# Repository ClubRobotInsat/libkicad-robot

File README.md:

# Kicad library of the Robot club at INSA Toulouse

## How to create a new component

1. Install the library on your computer
2. Use the footprint / symbol editor to create the components
3. Copy the components from the 3rd party folder (Preference -> Configure Paths -> KICAD7_3RD_PARTY) to this repository
4. Update the file VERSION to bump version and allows everyone to update the plugin

## How to bring 3D model

For 3D model it's a bit more complicated, you must add the model manualy in the correct folder in this repository and in the footprint editor 
refer to it with something like `${KICAD7_3RD_PARTY}/3dmodels/com_github_clubrobotinsat_libkicad-robot/Robot.3dshapes/YOURMODEL.step`

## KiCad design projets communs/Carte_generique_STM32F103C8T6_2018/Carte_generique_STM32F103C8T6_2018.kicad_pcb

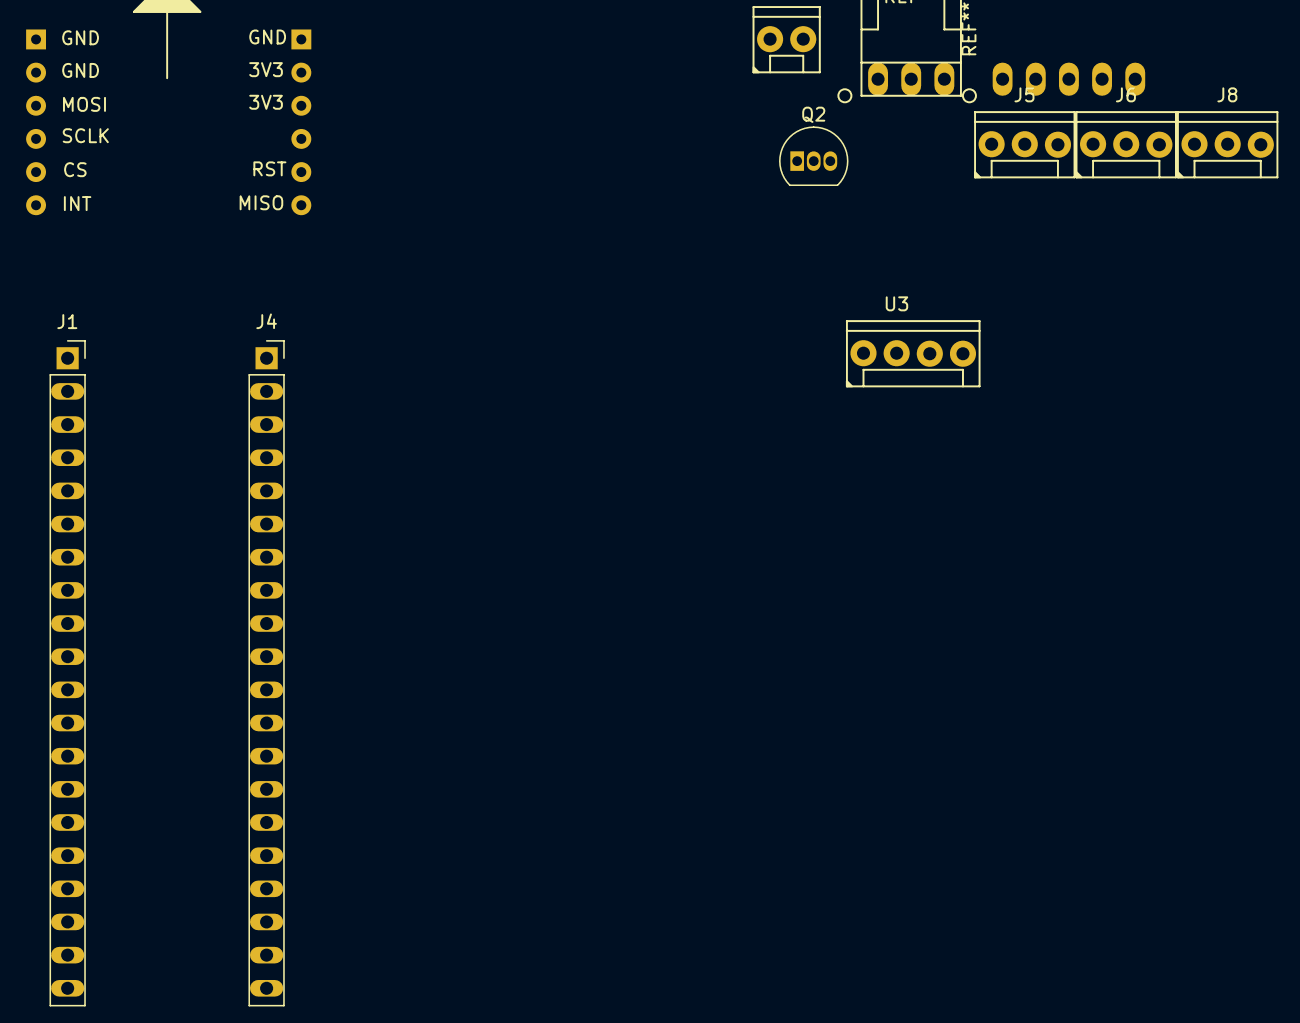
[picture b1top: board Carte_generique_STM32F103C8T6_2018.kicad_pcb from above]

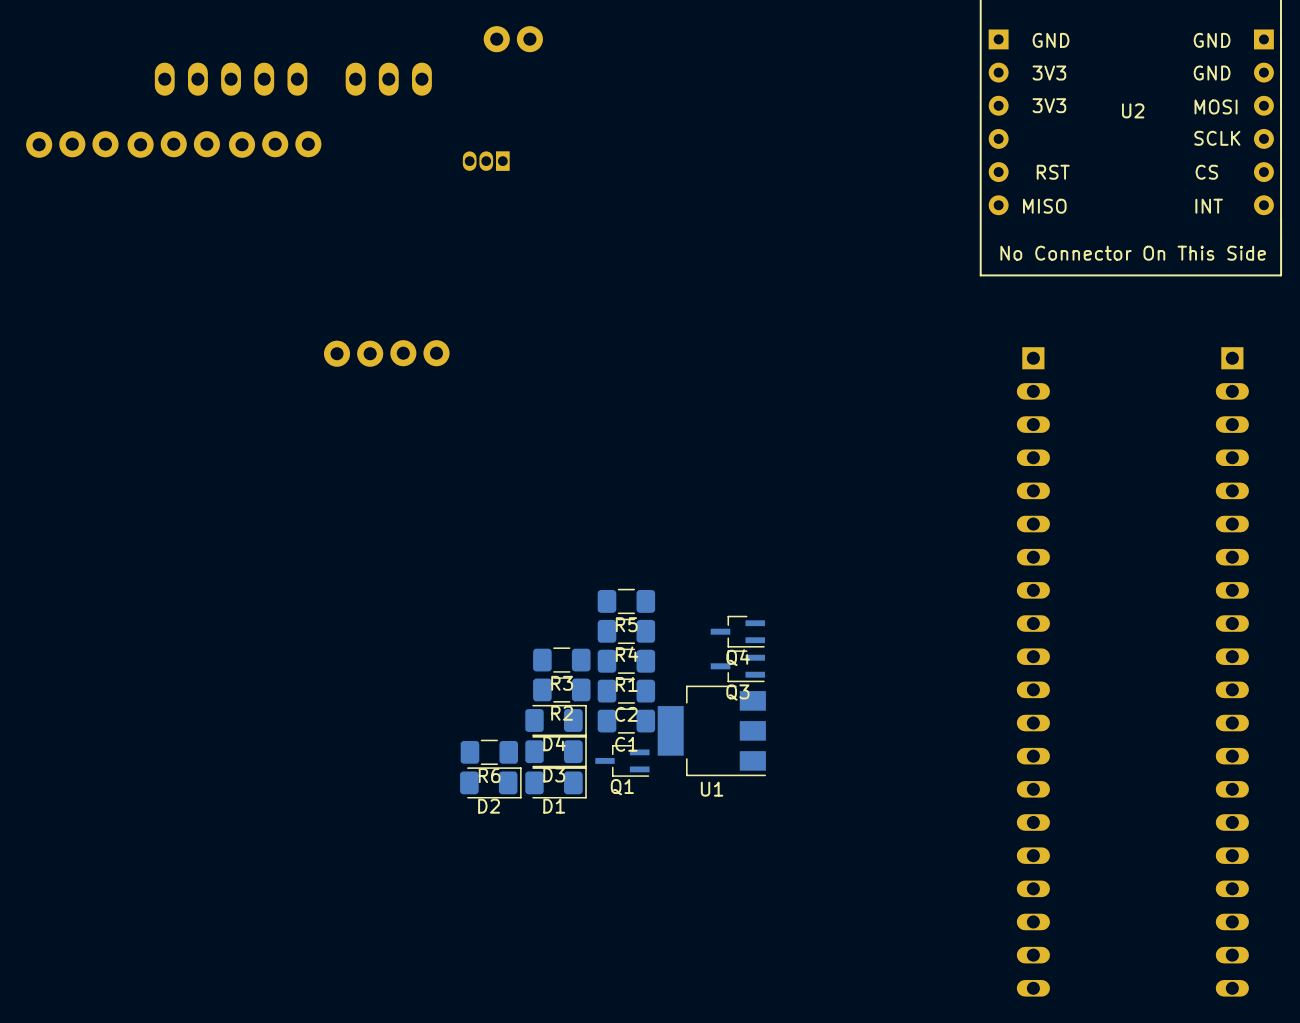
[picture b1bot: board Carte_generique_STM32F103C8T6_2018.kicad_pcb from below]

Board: 2 copper layers, 27 parts (16 on the bottom side), 12 nets, no tracks yet.

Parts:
C1, C2: 1u; C_1206_3216Metric_Pad1.42x1.75mm_HandSolder
D1: LED_hardfault_jaune; LED_1206_3216Metric_Pad1.42x1.75mm_HandSolder
D2: LED_communication_vert; LED_1206_3216Metric_Pad1.42x1.75mm_HandSolder
D3: led_feedback_vert; LED_1206_3216Metric_Pad1.42x1.75mm_HandSolder
D4: LED_alimentation_rouge; LED_1206_3216Metric_Pad1.42x1.75mm_HandSolder
J1, J4: Conn_01x20_Female; PinSocket_1x20_P2.54mm_Vertical_Long_Pads
J2: Alim puissance; HE14-2-straight
J3: Alim logique; HE14-3_horizontal
J5: PWM input; HE14-3-straight
J6: PWM output; HE14-3-straight
J7: QEI; HE14-5_horizontal
J8: Liaison serie; HE14-3-straight
Q1, Q3, Q4: PMF370XN; SOT-323_SC-70_Handsoldering
Q2: 2N7000; TO-92_Inline
R1, R4, R5, R6: 150; R_1206_3216Metric_Pad1.42x1.75mm_HandSolder
R2, R3: 10k; R_1206_3216Metric_Pad1.42x1.75mm_HandSolder
U1: TC1262-33; SOT-223-3_TabPin2
U2: w5500
U3: servo_connector; HE14-4-straight

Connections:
+3V3: C2.1, Q2.2, R2.1, U1.3, U2.10, U2.11
+5V: C1.1, J1.18, J3.2, J7.2, R1.1, R3.1, R4.1, R5.1, R6.1, U1.1
/3.3V_logic: Q2.1, R2.2
/5V_logic: Q2.3, R3.2
GND: C1.2, C2.2, D4.1, J1.19, J3.1, J4.1, J4.2, J5.1, J6.1, J7.1, J8.1, Q1.2, Q3.2, Q4.2, U1.2, U2.5, U2.6, U2.12, U3.1
unnamed: D1.1, Q1.3
unnamed: D1.2, R1.2
unnamed: D2.1, Q3.3
unnamed: D2.2, R4.2
unnamed: D3.1, Q4.3
unnamed: D3.2, R5.2
unnamed: D4.2, R6.2

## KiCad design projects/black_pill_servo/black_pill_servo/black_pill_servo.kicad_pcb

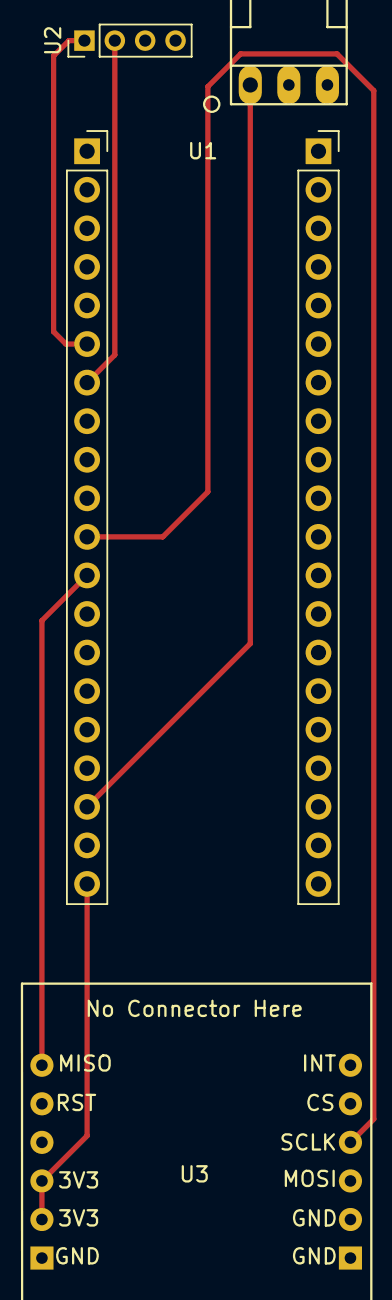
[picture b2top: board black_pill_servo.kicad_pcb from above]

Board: 2 copper layers, 4 parts (0 on the bottom side), 8 nets.

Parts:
J1: alim_logique_5V; HE14-3_horizontal
U1: black_pill
U2: servo_connector; PinHeader_1x04_P2.00mm_Vertical
U3: w5500

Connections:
+3V3: U1.20, U3.10, U3.11
+5V: J1.1, U1.18
GND: J1.2, U1.19, U1.21, U1.22, U2.4, U3.5, U3.6, U3.12
MISO: U1.12, U3.7
MOSI: U1.13, U3.4
PA9: U1.6, U2.1
PA10: U1.7, U2.2
SCLK: U1.11, U3.3

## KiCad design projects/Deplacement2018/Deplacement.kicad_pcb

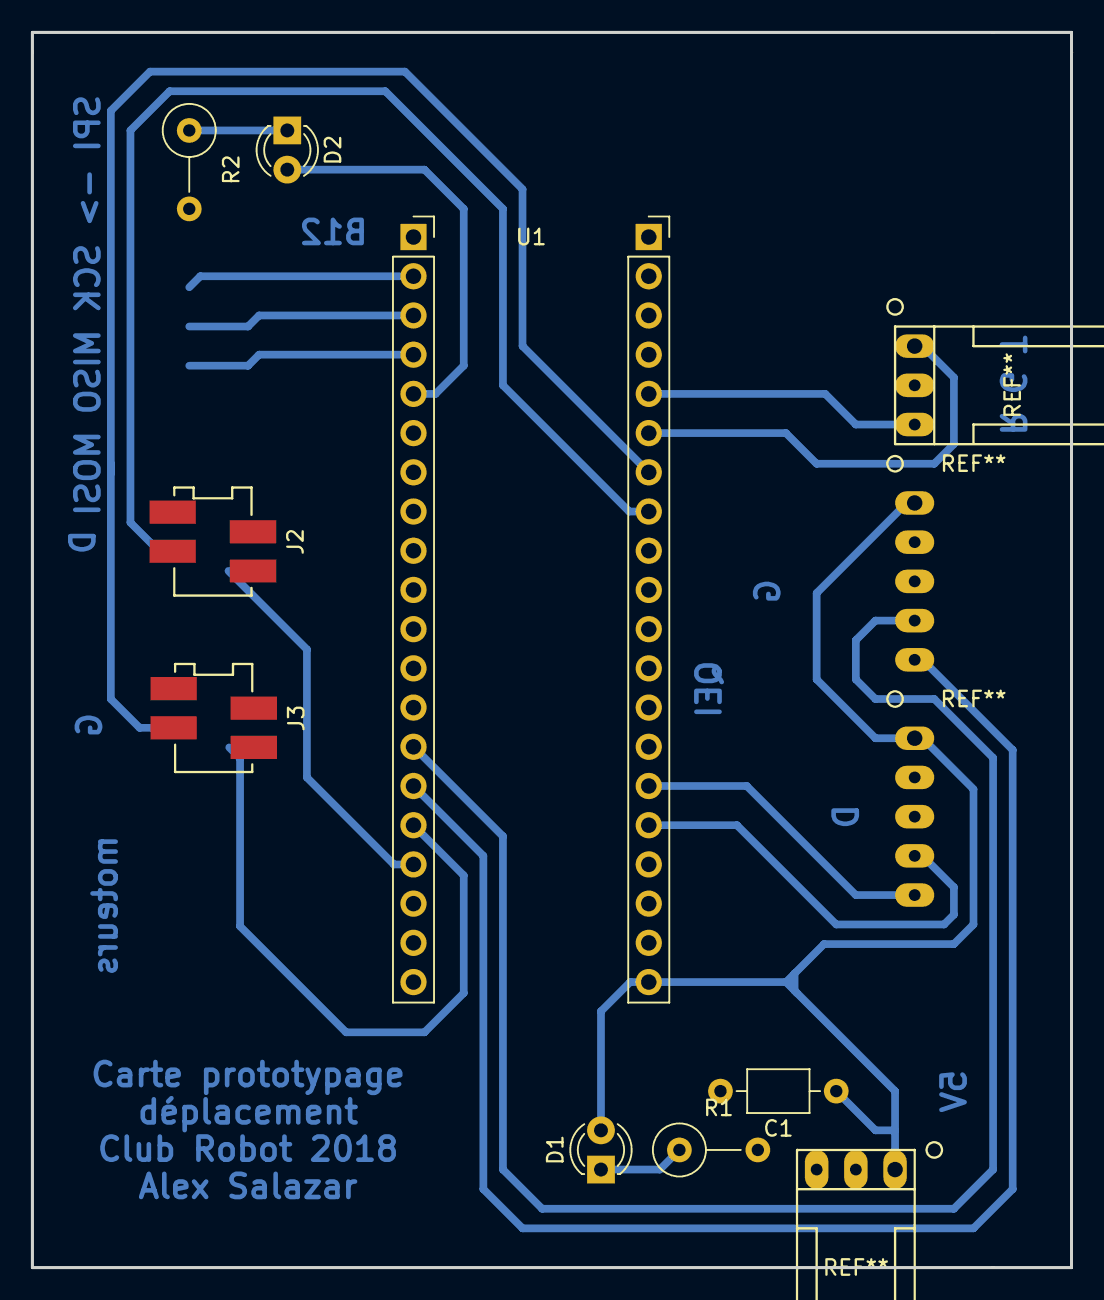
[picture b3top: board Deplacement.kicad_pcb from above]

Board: 2 copper layers, 67.3 x 80.0 mm, 12 parts (0 on the bottom side), 15 nets.

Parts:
C1: C; C_Axial_L3.8mm_D2.6mm_P7.50mm_Horizontal
D1, D2: LED; LED_D3.0mm
J1: alim_logique_5V; HE14-3_horizontal
J2: moteur_droit; ConnectorMicromatch-4
J3: moteur_gauche; ConnectorMicromatch-4
J4: Conn_01x03; HE14-3_horizontal
J5: QEI_droite; HE14-5_horizontal
J6: QEI_gauche; HE14-5_horizontal
R1, R2: R; R_Axial_DIN0309_L9.0mm_D3.2mm_P5.08mm_Vertical
U1: black_pill

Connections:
+5V: C1.1, D1.2, J1.1, J5.1, J6.1, U1.40
Direction_moteur_droit: J2.1, U1.17
Direction_moteur_gauche: J3.1, U1.16
GND: C1.2, J1.2, J2.3, J3.3, J4.2, J5.2, J6.2, R1.2, R2.2, U1.19, U1.21, U1.22
LED_feedback: D2.2, U1.5
unnamed: D1.1, R1.1
unnamed: D2.1, R2.1
PWM_moteur_droit: J2.2, U1.28
PWM_moteur_gauche: J3.2, U1.27
QEI_droite_1: J5.4, U1.36
QEI_droite_2: J5.5, U1.35
QEI_gauche_1: J6.4, U1.14
QEI_gauche_2: J6.5, U1.15
RX: J4.3, U1.25
TX: J4.1, U1.26

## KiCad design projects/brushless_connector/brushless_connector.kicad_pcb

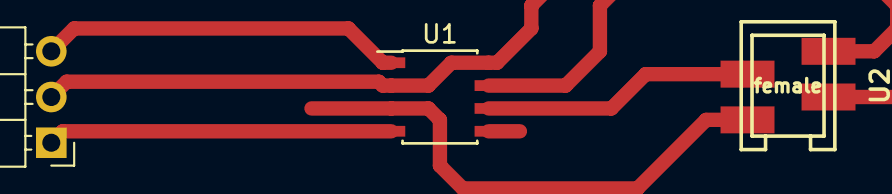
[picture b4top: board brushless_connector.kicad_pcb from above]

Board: 2 copper layers, 3 parts (0 on the bottom side), 6 nets.

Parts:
J1: Conn_01x03_Female; PinHeader_1x03_P2.54mm_Horizontal
U1: MCP2551-I-SN; SOIC-8_3.9x4.9mm_P1.27mm
U2: micromatch_female; 0-188275-4_SMD_4-pin_female

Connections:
GND: J1.2, U1.2, U1.8, U2.2
unnamed: J1.1, U1.4
unnamed: J1.3, U1.1
unnamed: U1.3, U2.1
unnamed: U1.6, U2.3
unnamed: U1.7, U2.4

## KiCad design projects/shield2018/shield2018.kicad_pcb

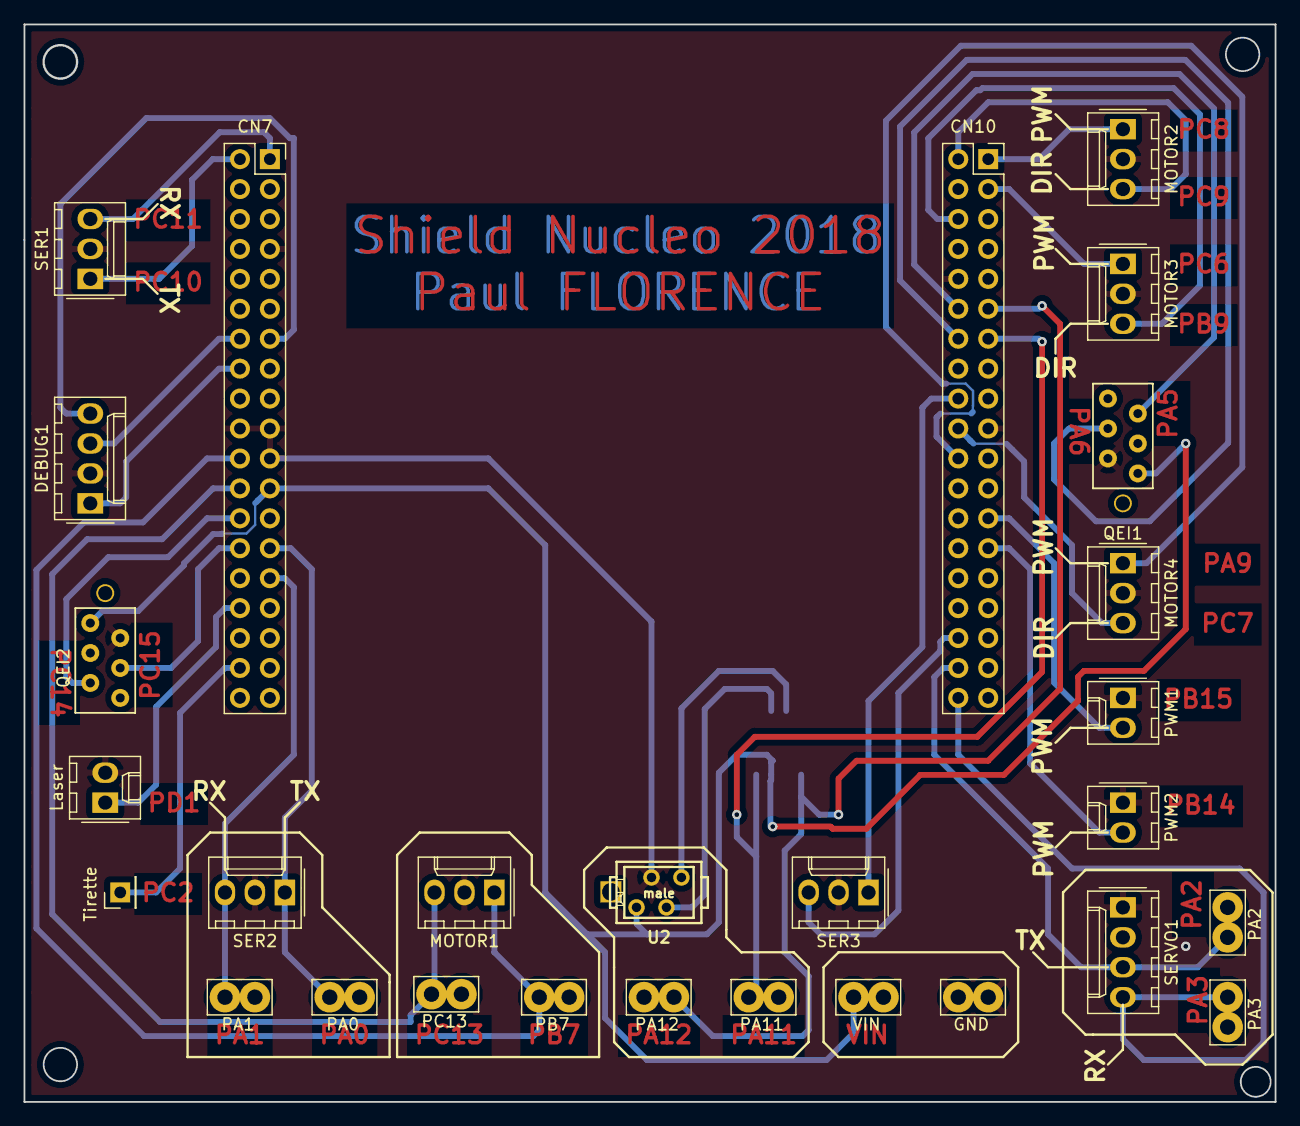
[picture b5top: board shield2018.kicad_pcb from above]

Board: 2 copper layers, 106.1 x 91.4 mm, 29 parts (1 on the bottom side), 33 nets.

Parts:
CN7, CN10: CONN_02X19; PinSocket_2x19_P2.54mm_Vertical_Odd
DEBUG1: Connection ST-LINK; Molex_KK-254_AE-6410-04A_1x04_P2.54mm_Vertical
GND: GND; TestPoint_Bridge_Pitch2.54mm_Drill1.3mm
Laser: Conn_01x02; Molex_KK-254_AE-6410-02A_1x02_P2.54mm_Vertical
MCP2551: MCP2551; SOIC-8_3.9x4.9mm_P1.27mm
MOTOR1: Motor1; Molex_KK-254_AE-6410-03A_1x03_P2.54mm_Vertical
MOTOR2: Motor2; Molex_KK-254_AE-6410-03A_1x03_P2.54mm_Vertical
MOTOR3: Motor3; Molex_KK-254_AE-6410-03A_1x03_P2.54mm_Vertical
MOTOR4: Motor4; Molex_KK-254_AE-6410-03A_1x03_P2.54mm_Vertical
PA0: TX2; TestPoint_Bridge_Pitch2.54mm_Drill1.3mm
PA1: RX2; TestPoint_Bridge_Pitch2.54mm_Drill1.3mm
PA2: TX_SERVO; TestPoint_Bridge_Pitch2.54mm_Drill1.3mm
PA3: RX_SERVO; TestPoint_Bridge_Pitch2.54mm_Drill1.3mm
PA11: CAN_RD; TestPoint_Bridge_Pitch2.54mm_Drill1.3mm
PA12: CAN_TD; TestPoint_Bridge_Pitch2.54mm_Drill1.3mm
PB7: PWM_MOT_1; TestPoint_Bridge_Pitch2.54mm_Drill1.3mm
PC13: DIR_MOT_1; TestPoint_Bridge_Pitch2.54mm_Drill1.3mm
PWM1: Pwm 1; Molex_KK-254_AE-6410-02A_1x02_P2.54mm_Vertical
PWM2: Pwm 2; Molex_KK-254_AE-6410-02A_1x02_P2.54mm_Vertical
QEI1, QEI2: micromatch_6_female; Micromatch_Female_6
SER1: Serial 1; Molex_KK-254_AE-6410-03A_1x03_P2.54mm_Vertical
SER2: Serial 2; Molex_KK-254_AE-6410-03A_1x03_P2.54mm_Vertical
SER3: Serial 3; Molex_KK-254_AE-6410-03A_1x03_P2.54mm_Vertical
SERVO1: Servo 1; Molex_KK-254_AE-6410-04A_1x04_P2.54mm_Vertical
Tirette: Digital In 1; PinHeader_1x01_P2.54mm_Vertical
U2: micromatch_female; 0-215464-4_TH_4-pin_male
VIN: 5V; TestPoint_Bridge_Pitch2.54mm_Drill1.3mm

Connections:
CAN_HIGH: MCP2551.7, U2.4
CAN_LOW: MCP2551.6, U2.3
GND: CN7.8, CN7.19, CN7.20, CN7.22, CN10.9, CN10.20, DEBUG1.2, GND.1, Laser.2, MCP2551.2, MCP2551.8, MOTOR1.2, MOTOR2.2, MOTOR3.2, MOTOR4.2, PWM1.1, PWM2.1, QEI1.5, QEI2.5, SER1.2, SER2.2, SER3.2, SERVO1.1, U2.2
PA0: CN7.28, PA0.1, SER2.1
PA1: CN7.30, PA1.1, SER2.3
PA2: CN10.35, PA2.1, SERVO1.3
PA3: CN10.37, PA3.1, SERVO1.4
PA5: CN10.11, QEI1.2
PA6: CN10.13, QEI1.3
PA9: CN10.21, MOTOR4.1
PA10: CN10.33, SER3.3
PA11: CN10.14, MCP2551.4, PA11.1
PA12: CN10.12, MCP2551.1, PA12.1
PA13: CN7.13, DEBUG1.3
PB6: CN10.17, SER3.1
PB7: CN7.21, MOTOR1.1, PB7.1
PB9: CN10.5, MOTOR3.3
PB14: CN10.28, PWM2.2
PB15: CN10.26, PWM1.2
PC2: CN7.35, Tirette.1
PC6: CN10.4, MOTOR3.1
PC7: CN10.19, MOTOR4.3
PC8: CN10.2, MOTOR2.1
PC9: CN10.1, MOTOR2.3
PC10: CN7.1, SER1.1
PC11: CN7.2, SER1.3
PC13: CN7.23, MOTOR1.3, PC13.1
PC14: CN7.25, QEI2.2
PC15: CN7.27, QEI2.3
PD1: CN7.31, Laser.1
RESET: CN7.14, DEBUG1.4
T_SCK: CN7.15, DEBUG1.1
VIN: CN7.24, MCP2551.3, QEI1.6, QEI2.6, U2.1, VIN.1

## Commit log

2018-05-20 Attributes.
2018-05-20 Projet.
2018-06-02 Maj Librairie
2018-06-19 Fix de l'oubli de quelques via.
2018-10-25 Ignore fichiers temporaires OSX
2018-10-25 ajout black pill
2018-10-26 Correction types de pin
2018-10-26 import des vielles libs eagle
2018-10-26 nouveaux connecteurs
2018-10-27 meilleurs connecteurs
2018-10-27 Ajout des descriptions
2018-10-28 HE13-3 en silk
2018-10-28 connecteur HE13 en 3d
2018-10-28 Updated .gitignore and .gitattributes. Added a script to generate better diff with kicad.
2018-10-28 Renamed setup_kicad to setup_git.
2018-10-28 Utilisation d'un PATH pour la 3d
2018-10-31 correction des layers
2018-10-31 footprint de la BP
2018-11-01 maj HE14
2018-11-01 Nouvelle carte deplacement
2018-11-01 correction blackpill
2018-11-01 labels places
2018-11-01 composants places
2018-11-01 maj pour la carte deplacement
2018-11-01 proto deplacement terminé
2018-11-01 cleanup de doublon
2018-11-02 Changed permission on the setup script. Fixed two components : * micromatch_4 now has a "staircase" layout to better represent the connector * removed the fifth connection from roue_codeuse because i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
2018-11-03 Nouveau projet de test des libs
2018-11-03 Fixed QEI inversion.
2018-11-03 fix sur deplacement
2018-11-03 maj pcb
2018-11-04 Rename des libs
2018-11-04 Added a new template for bare-metal stm32f103.
2018-11-04 Fixed last-update date.
2018-11-10 Better footprints for micromatch. Added a 3D model library to the club models.
2018-11-11 Better footprints and 3D view. Added a new project : black_pill servo.
2018-11-11 Updated schematic & PCB for servo card.
2018-11-14 Created 'blocs' repo to store elementary functions to be included on future PCBs
2018-11-15 controlled_led termine
2018-11-15 Created the generic PCB project
2018-11-15 Added datasheets.
2018-11-15 added power and led
2018-11-15 added connectors
2018-11-25 Removed out of date Deplacement2018 projects. Fixed robot library for black_pill. Added a ready to use schematic bloc for LEDs.
2018-12-06 cleanup, added power and connectors to the generic board
2018-12-06 minor corrections in the power supply
2018-12-06 Ajout connecteurs black pill
2018-12-13 new 3.3 regulator
2018-12-13 Ajout de footprints
2018-12-13 renamed LEDs
2018-12-13 set leds footprints
2018-12-20 Ajout power flags
2018-12-20 Correction labelles blackpill
2018-12-20 ajout HE14-2 libkicad
2018-12-20 modif HE14-3 -5 taille percages
2018-12-27 cleaned repository structure
2019-01-09 new (better) pinsocket for our usages
2019-01-09 LED are now driven by MOSFETs
2019-01-09 Now uses the new blackpill connectors
2019-01-13 new HE14 footprint+3Dmodel
2019-01-13 added 3Dshape with a kicad path
2019-01-13 added 3D shape for horizontal HE14
2019-01-17 corrected pin diameter en HE14 straight
2019-01-17 Removed obsolete connectors
2019-01-20 update w5500 footprint
2019-01-20 fix the w5500 footprint
2019-01-20 Fix w5500 courtyard
2019-01-20 added QEI connector
2019-01-20 prepared the generic footprint
2019-01-20 forgot to save
2019-01-20 removed outdated info and adder the club's header
2019-01-20 fixed header typo
2019-01-20 added HE14-4 footprint
2019-01-20 assigned the connector-servo footprint
2019-01-20 harmonised servo-connector with the new pinout conventions
2019-01-20 moved the led-communication to a generic pin
2019-01-20 added the blackpill actual courtyard
2019-01-20 changed the power connector footprint
2019-01-24 Fix wrong line ending
2019-01-24 Better raw f103
2019-01-31 update our generic's card name and some of its courtyard issues
2019-01-31 move around some footprints
2019-01-31 ajout HE14-5
2019-01-31 fix a small header mistake
2019-02-05 Fix Wrong pinout for w5500
2019-05-16 Rajout lib PTH08080W
2019-05-16 Improve drill size for W5500 vias
2019-05-16 Add more copper around w5500 pins
2019-05-17 Add phoenix connectors
2022-06-29 test
2022-06-29 test of footprint
2022-07-02 Add power connector
2022-07-02 Power connector
2022-07-03 Ajout JCK
2022-07-03 Oups
2022-07-04 Add JCK
2022-07-04 Add Blue pill
2022-07-23 Add HE14, USBA; Update JCK
2022-12-08 Add first part of L9958
2022-12-08 Add L9958
2022-12-09 Add nucleo32
2023-02-17 Update to Kicad 7
2023-02-17 Bump version
2023-02-17 Edit script
2023-02-17 Typo
